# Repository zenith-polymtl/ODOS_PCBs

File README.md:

# ODOS\_PCBs

##### 4 PCBS : 

* PDB 5V
* PDB 12V
* PDB propulsion
* PCB Payload

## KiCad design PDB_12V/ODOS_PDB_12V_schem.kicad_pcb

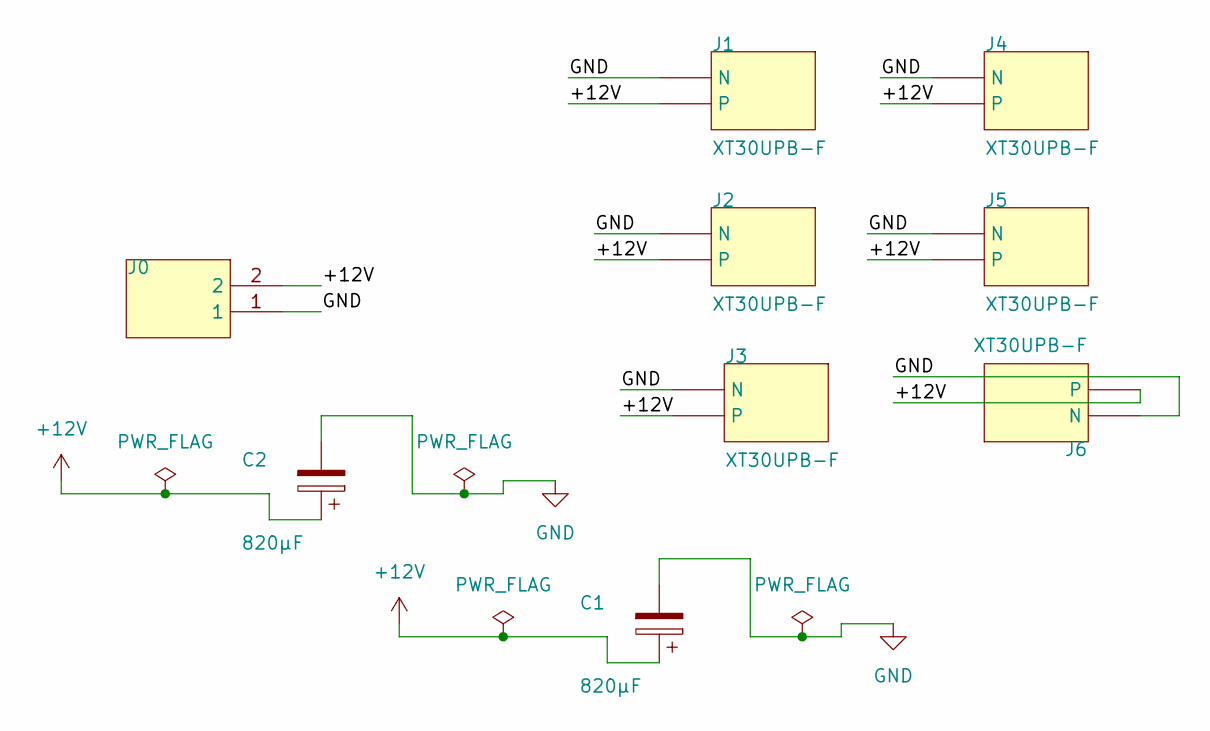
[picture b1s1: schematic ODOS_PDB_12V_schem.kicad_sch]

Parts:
C1, C2: 820µF; CP_Elec_10x10.5; MANUFACTURER_PART_NUMBER EEE-FN1E821UP
J0: AMASS_XT30UPB-M_1x02_P5.0mm_Vertical; MANUFACTURER_PART_NUMBER XT30UPB-M
J1, J2, J3, J4, J5, J6: XT30UPB-F; AMASS_XT30UPB-F_1x02_P5.0mm_Vertical; MANUFACTURER_PART_NUMBER XT30UPB-F

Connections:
+12V: C1.1, C2.1, J0.2, J1.2, J2.2, J3.2, J4.2, J5.2, J6.2
GND: C1.2, C2.2, J0.1, J1.1 (N), J2.1 (N), J3.1 (N), J4.1 (N), J5.1 (N), J6.1 (N)

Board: 2 copper layers, 9 parts (0 on the bottom side), 2 nets, no tracks yet.
